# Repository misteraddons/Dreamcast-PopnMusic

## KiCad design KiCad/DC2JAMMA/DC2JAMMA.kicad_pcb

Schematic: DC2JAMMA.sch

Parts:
D1, D2: BAT54S; D_SOT-23_ANK; LCSC Part C408389
J1, J3, J6, J7: Conn_01x02; PinHeader_1x02_P2.54mm_Vertical; LCSC Part C358684
J2, J4: Conn_01x05; TerminalBlock_RND_205-00015_1x05_P5.00mm_Horizontal; LCSC Part C192780
J5: Conn_02x20_Odd_Even; PinSocket_2x20_P2.54mm_Vertical; LCSC Part C429965
Logo1: MiSTer_Addons_Logo; MiSTer_Addons_copper_15mm
RN2, RN3, RN4, RN5, RN6, RN7: 10K_4xArray; R_Array_Convex_4x0402; LCSC Part C25725
U1, U2: Pico; RPi_Pico_SMD_TH
U3, U4, U5, U6, U7, U8: TVS_RCLAMP0524P-N; UDFN-10_1.35x2.6mm_P0.5mm; LCSC Part C316044

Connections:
+3V3: J5.3
+5V: J5.1, J5.2
/BLUE_IN: J5.9, J5.10
/COIN_METER_1: J5.4
/GREEN_IN: J5.7, J5.8
/P1A: J5.32, RN4.5 (R4.2), U6.1 (IO1), U6.10 (N/C)
/P1A_ATTEN: RN4.4 (R4.1), U2.10 (GPIO7)
/P1B: J5.34, RN4.7 (R2.2), U6.4 (IO3), U6.7 (N/C)
/P1B7: J5.11
/P1B8: J5.12
/P1B_ATTEN: RN4.2 (R2.1), U2.11 (GPIO8)
/P1C: J5.36, RN6.5 (R4.2), U8.1 (IO1), U8.10 (N/C)
/P1COIN: J5.14
/P1C_ATTEN: J1.1, RN6.4 (R4.1), U2.12 (GPIO9)
/P1DOWN: J5.20, RN5.5 (R4.2), U5.1 (IO1), U5.10 (N/C)
/P1DOWN_ATTEN: RN5.4 (R4.1), U2.5 (GPIO3)
/P1LEFT: J5.22, RN5.7 (R2.2), U5.4 (IO3), U5.7 (N/C)
/P1LEFT_ATTEN: RN5.2 (R2.1), U2.6 (GPIO4)
/P1LT_ATTEN: J3.2, U2.21 (GPIO16)
/P1RIGHT: J5.24, RN7.5 (R4.2), U7.1 (IO1), U7.10 (N/C)
/P1RIGHT_ATTEN: RN7.4 (R4.1), U2.7 (GPIO5)
/P1RT_ATTEN: J1.2, U2.22 (GPIO17)
/P1RX: U2.2 (GPIO1)
/P1START: J5.16, RN3.5 (R4.2), U3.1 (IO1), U3.10 (N/C)
/P1START_ATTEN: RN3.4 (R4.1), U2.9 (GPIO6)
/P1TX: U2.1 (GPIO0)
/P1UP: J5.18, RN3.7 (R2.2), U3.4 (IO3), U3.7 (N/C)
/P1UP_ATTEN: RN3.2 (R2.1), U2.4 (GPIO2)
/P1X: J5.26, RN7.7 (R2.2), U7.4 (IO3), U7.7 (N/C)
/P1X_ATTEN: RN7.2 (R2.1), U2.14 (GPIO10)
/P1Y: J5.28, RN2.5 (R4.2), U4.1 (IO1), U4.10 (N/C)
/P1Y_ATTEN: RN2.4 (R4.1), U2.15 (GPIO11)
/P1Z: J5.30, RN2.7 (R2.2), U4.4 (IO3), U4.7 (N/C)
/P1Z_ATTEN: J3.1, RN2.2 (R2.1), U2.16 (GPIO12)
/P1_ANALOG_HOR_1: U2.24 (GPIO18)
/P1_ANALOG_VER_1: U2.25 (GPIO19)
/P1_MAPLE_PIN1: J4.1, U2.19 (GPIO14)
/P1_MAPLE_PIN5: J4.5, U2.20 (GPIO15)
/P2A: J5.31, RN4.6 (R3.2), U6.2 (IO2), U6.9 (N/C)
/P2A_ATTEN: RN4.3 (R3.1), U1.10 (GPIO7)
/P2B: J5.33, RN4.8 (R1.2), U6.5 (IO4), U6.6 (N/C)
/P2B7: J5.37
/P2B8: J5.38
/P2B_ATTEN: RN4.1 (R1.1), U1.11 (GPIO8)
/P2C: J5.35, RN6.6 (R3.2), U8.2 (IO2), U8.9 (N/C)
/P2COIN: J5.13
/P2C_ATTEN: J6.1, RN6.3 (R3.1), U1.12 (GPIO9)
/P2DOWN: J5.19, RN5.6 (R3.2), U5.2 (IO2), U5.9 (N/C)
/P2DOWN_ATTEN: RN5.3 (R3.1), U1.5 (GPIO3)
/P2LEFT: J5.21, RN5.8 (R1.2), U5.5 (IO4), U5.6 (N/C)
/P2LEFT_ATTEN: RN5.1 (R1.1), U1.6 (GPIO4)
/P2LT_ATTEN: J7.2, U1.21 (GPIO16)
/P2RIGHT: J5.23, RN7.6 (R3.2), U7.2 (IO2), U7.9 (N/C)
/P2RIGHT_ATTEN: RN7.3 (R3.1), U1.7 (GPIO5)
/P2RT_ATTEN: J6.2, U1.22 (GPIO17)
/P2RX: U1.2 (GPIO1)
/P2START: J5.15, RN3.6 (R3.2), U3.2 (IO2), U3.9 (N/C)
/P2START_ATTEN: RN3.3 (R3.1), U1.9 (GPIO6)
/P2TX: U1.1 (GPIO0)
/P2UP: J5.17, RN3.8 (R1.2), U3.5 (IO4), U3.6 (N/C)
/P2UP_ATTEN: RN3.1 (R1.1), U1.4 (GPIO2)
/P2X: J5.25, RN7.8 (R1.2), U7.5 (IO4), U7.6 (N/C)
/P2X_ATTEN: RN7.1 (R1.1), U1.14 (GPIO10)
/P2Y: J5.27, RN2.6 (R3.2), U4.2 (IO2), U4.9 (N/C)
/P2Y_ATTEN: RN2.3 (R3.1), U1.15 (GPIO11)
/P2Z: J5.29, RN2.8 (R1.2), U4.5 (IO4), U4.6 (N/C)
/P2Z_ATTEN: J7.1, RN2.1 (R1.1), U1.16 (GPIO12)
/P2_ANALOG_HOR_1: U1.24 (GPIO18)
/P2_ANALOG_VER_1: U1.25 (GPIO19)
/P2_MAPLE_PIN1: J2.1, U1.19 (GPIO14)
/P2_MAPLE_PIN5: J2.5, U1.20 (GPIO15)
/RED_IN: J5.5, J5.6
GND: J2.3, J2.4, J4.3, J4.4, J5.39, J5.40, U1.3 (GND), U1.8 (GND), U1.13 (GND), U1.18 (GND), U1.23 (GND), U1.28 (GND), U1.38 (GND), U1.42 (GND), U2.3 (GND), U2.8 (GND), U2.13 (GND), U2.18 (GND), U2.23 (GND), U2.28 (GND), U2.38 (GND), U2.42 (GND), U3.3 (GND), U3.8 (GND), U4.3 (GND), U4.8 (GND), U5.3 (GND), U5.8 (GND), U6.3 (GND), U6.8 (GND), U7.3 (GND), U7.8 (GND), U8.3 (GND), U8.8 (GND)
unnamed: D1.1 (K), U1.39 (VSYS)
unnamed: D2.1 (K), U2.39 (VSYS)
VCC: D2.2 (A), J4.2
VDD: D1.2 (A), J2.2

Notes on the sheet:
ESD PROTECTION TVS DIODES AND RESISTORS

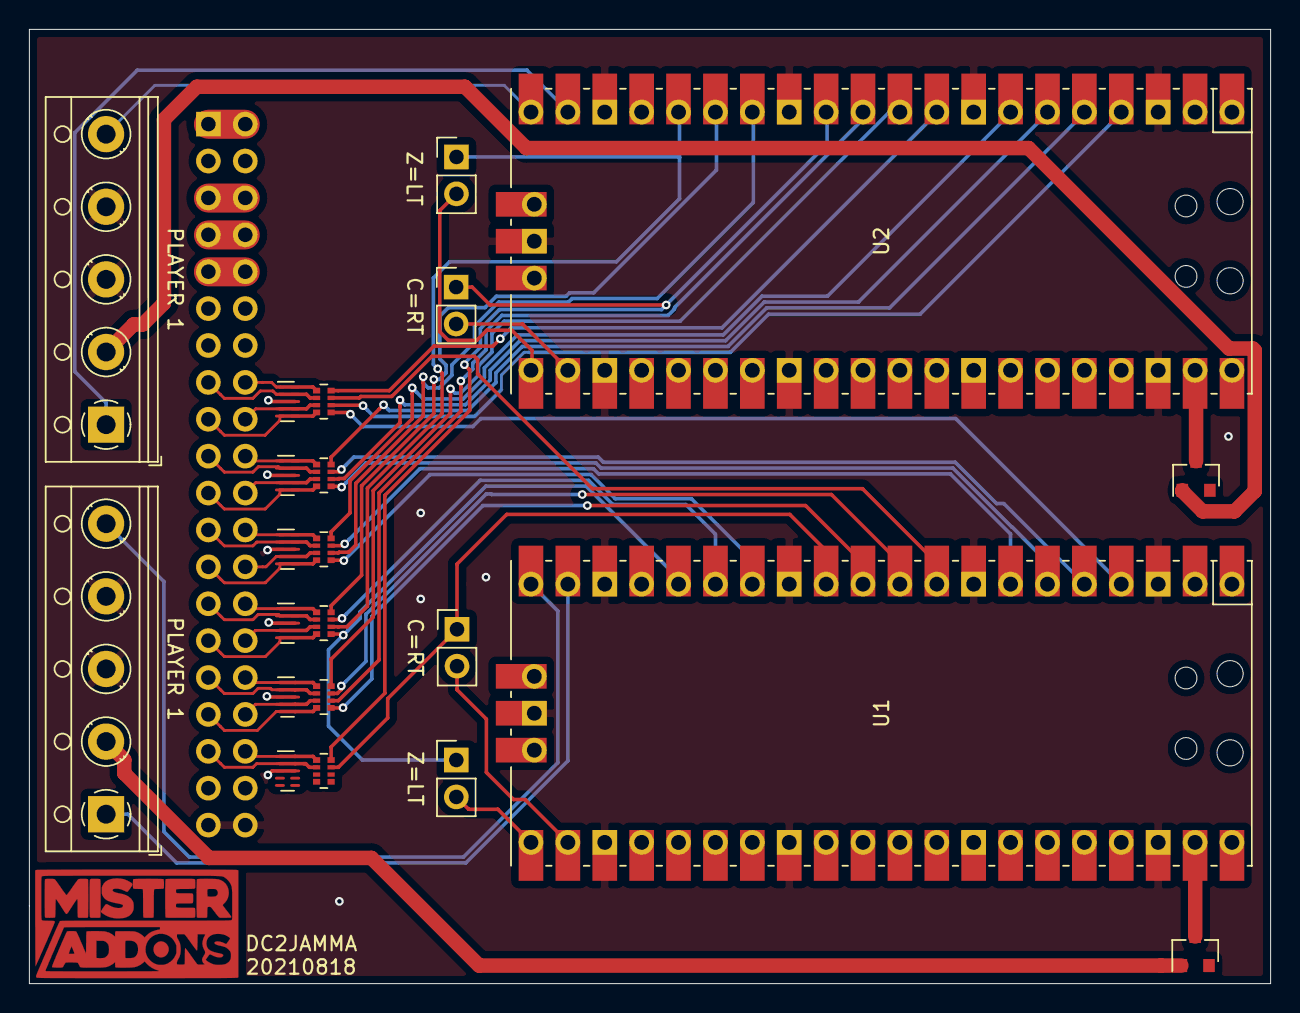
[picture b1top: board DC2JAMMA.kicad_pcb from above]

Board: 2 copper layers, 85.4 x 65.7 mm, 24 parts (1 on the bottom side), 61 nets.

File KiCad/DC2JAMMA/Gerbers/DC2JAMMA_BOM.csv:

Comment,Designator,Footprint,LCSC Part #
BAT54S Schottky diode,"D1,D2",D_SOT-23_ANK,C408389
"Conn_01x05 Generic connector, single row, 01x05, script generated (kicad-library-utils/schlib/autogen/connector/)","J2,J4",TerminalBlock_RND_205-00015_1x05_P5.00mm_Horizontal,C192780
"Conn_02x20_Odd_Even Generic connector, double row, 02x20, odd/even pin numbering scheme (row 1 odd numbers, row 2 even numbers), script generated (kicad-library-utils/schlib/autogen/connector/)",J5,PinSocket_2x20_P2.54mm_Vertical,C429965
"Conn_01x02 Generic connector, single row, 01x02, script generated (kicad-library-utils/schlib/autogen/connector/)","J6,J7,J1,J3",PinHeader_1x02_P2.54mm_Vertical,C358684
MiSTer_Addons_Logo ,Logo1,MiSTer_Addons_copper_15mm,-
"10K_4xArray 4 resistor network, parallel topology, DIP package","RN6,RN2,RN5,RN4,RN7,RN3",R_Array_Convex_4x0402,C25725
Pico ,"U1,U2",RPi_Pico_SMD_TH,-
TVS_RCLAMP0524P-N ,"U4,U8,U3,U5,U6,U7",UDFN-10_1.35x2.6mm_P0.5mm,C316044

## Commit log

2021-08-16 Preliminary support for Joystick, and Controller
2021-08-18 New KiCAD PCB and updated code
